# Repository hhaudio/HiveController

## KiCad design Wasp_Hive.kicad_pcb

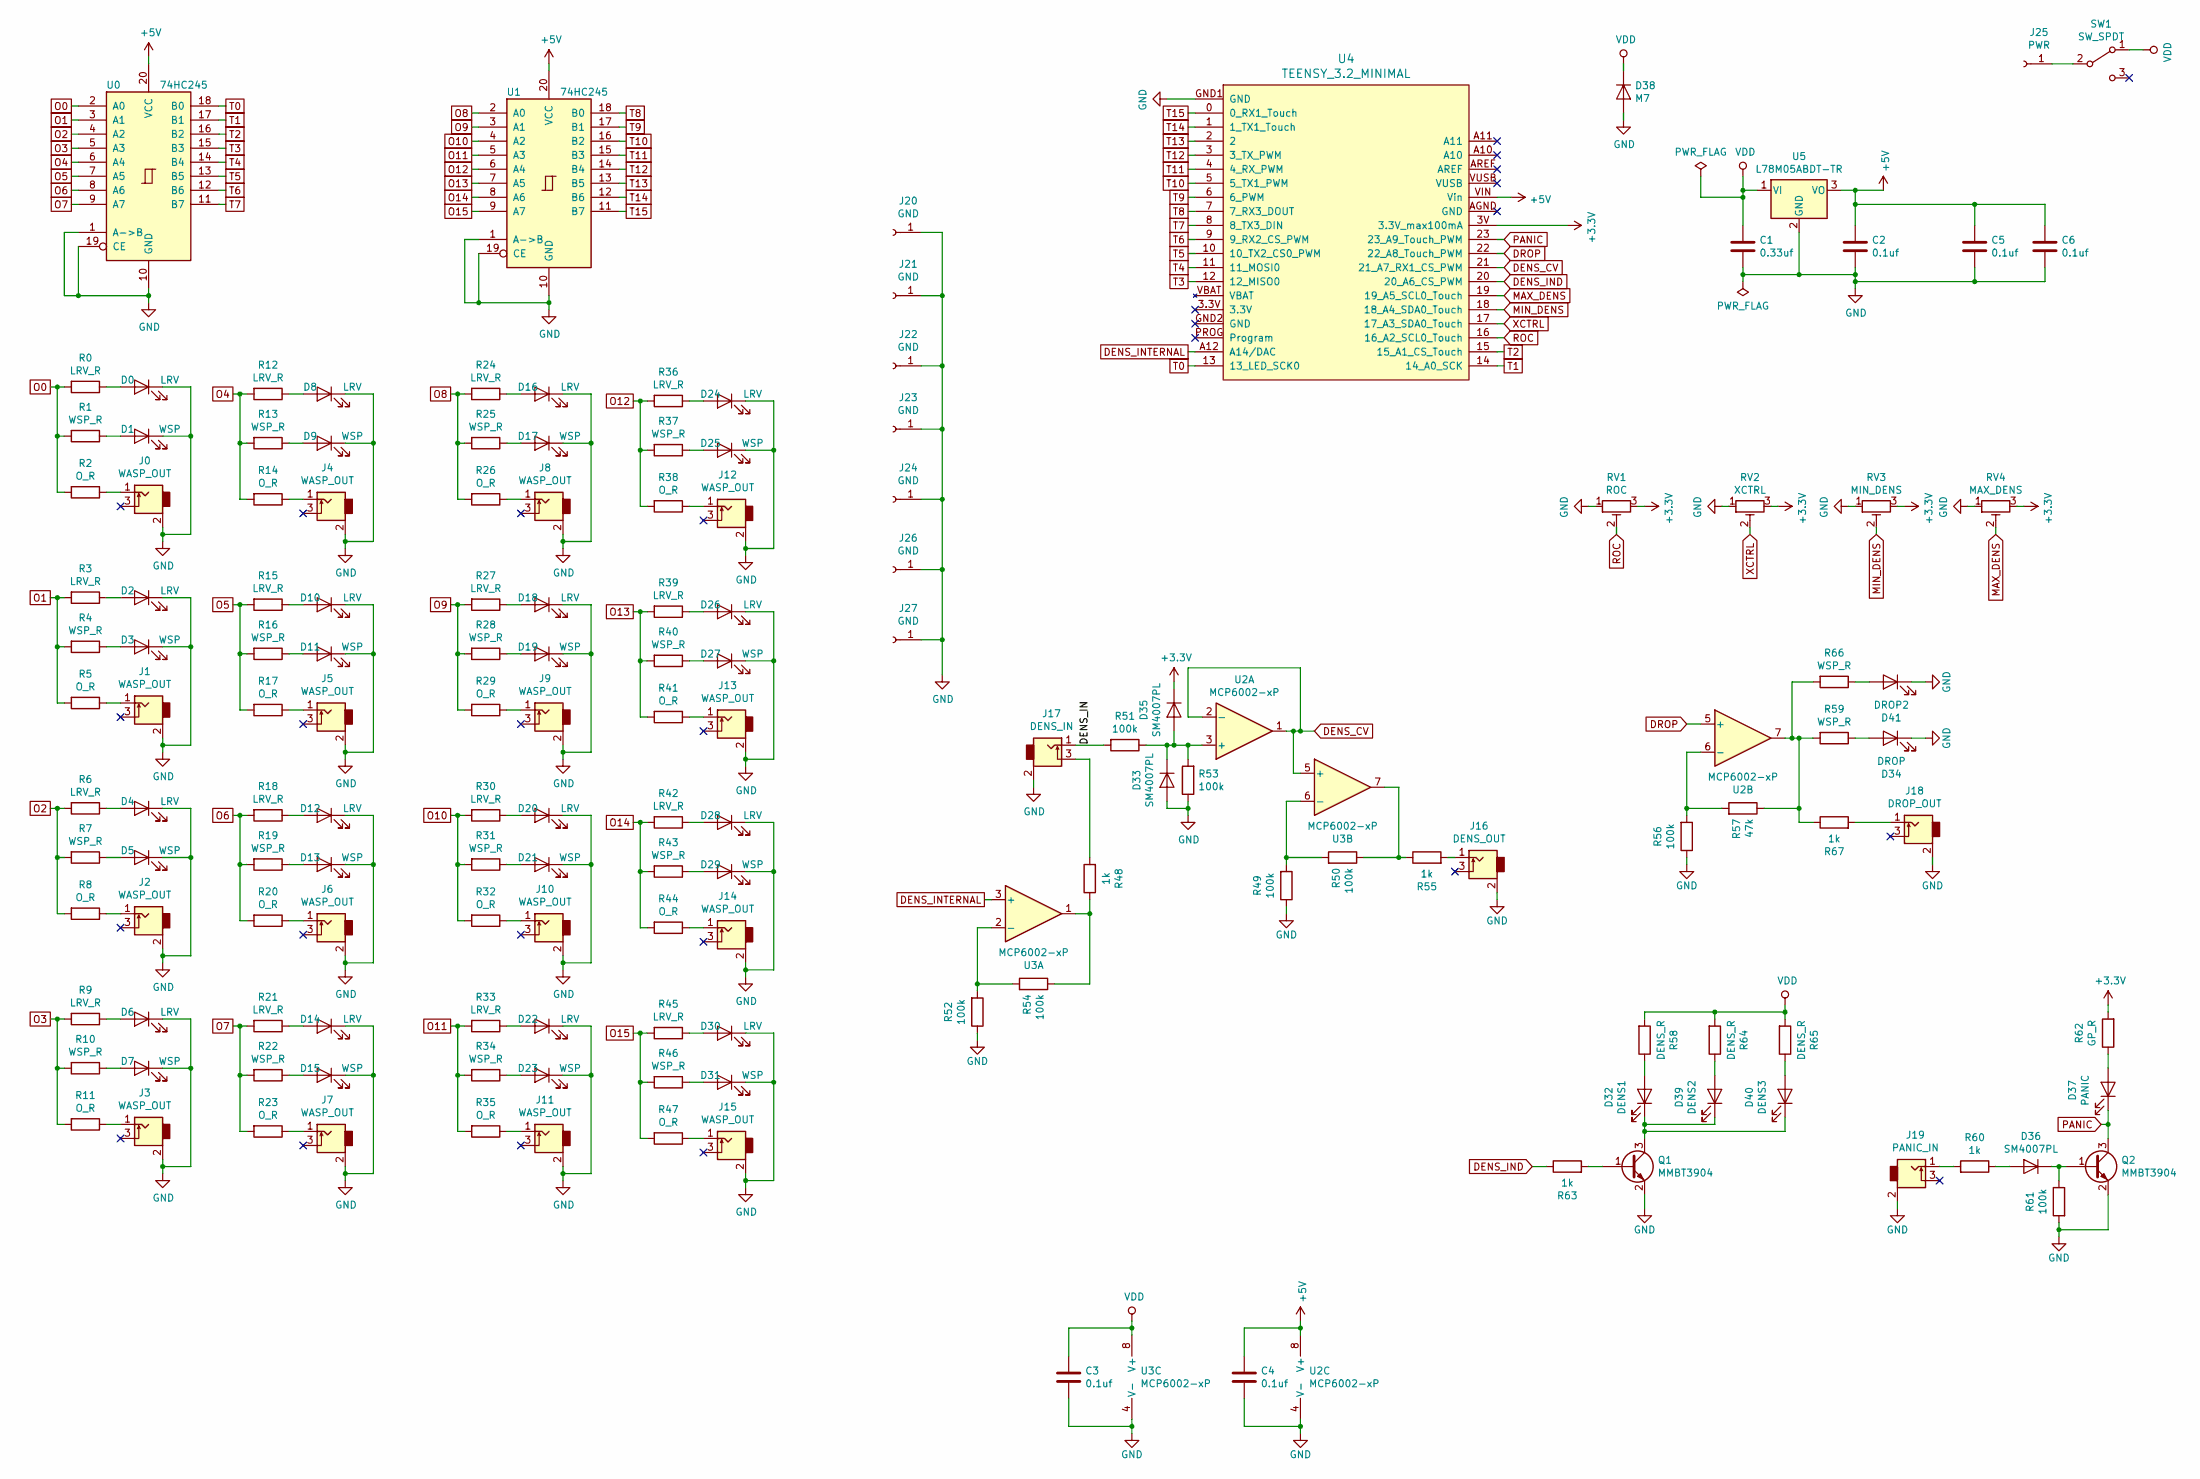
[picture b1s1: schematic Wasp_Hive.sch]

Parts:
C1: 0.33uf; C_0603_1608Metric_Pad1.05x0.95mm_HandSolder_SmallRef_Fab
C2, C3, C4, C5, C6: 0.1uf; C_0603_1608Metric_Pad1.05x0.95mm_HandSolder_SmallRef_Fab
D0, D2, D4, D6, D8, D10, D12, D14, D16, D18, D20, D22, D24, D26, D28, D30: LRV; Backlit_Larvae_Smaller
D1, D3, D5, D7, D9, D11, D13, D15, D17, D19, D21, D23, D25, D27, D29, D31: WSP; LED_1206_3216Metric_Pad1.42x1.75mm_HandSolder_FabRef
D32: DENS1; LED_1206_3216Metric_Pad1.42x1.75mm_HandSolder_FabRef
D33, D35, D36: SM4007PL; D_SOD-123
D34: DROP; LED_1206_3216Metric_Pad1.42x1.75mm_HandSolder_FabRef
D37: PANIC; LED_1206_3216Metric_Pad1.42x1.75mm_HandSolder_FabRef
D38: M7; D_SMA
D39: DENS2; LED_1206_3216Metric_Pad1.42x1.75mm_HandSolder_FabRef
D40: DENS3; LED_1206_3216Metric_Pad1.42x1.75mm_HandSolder_FabRef
D41: DROP2; LED_1206_3216Metric_Pad1.42x1.75mm_HandSolder_FabRef
J0, J1, J2, J3, J4, J5, J6, J7, J8, J9, J10, J11, J12, J13, J14, J15: WASP_OUT; EuroJack_Hex_SmallHoles_NoSilk_Clearance
J16: DENS_OUT; EuroJack_MonoSW_THT_NOREF_Mask_SmallHoles_NoSilk
J17: DENS_IN; EuroJack_MonoSW_THT_NOREF_Mask_SmallHoles_NoSilk
J18: DROP_OUT; EuroJack_MonoSW_THT_NOREF_Mask_SmallHoles_NoSilk
J19: PANIC_IN; EuroJack_MonoSW_THT_NOREF_Mask_SmallHoles_NoSilk
J20, J21, J22, J23, J24, J26, J27: GND; M3_Plated
J25: PWR; M3_Plated
Q1, Q2: MMBT3904; SOT-23
R0, R3, R6, R9, R12, R15, R18, R21, R24, R27, R30, R33, R36, R39, R42, R45: LRV_R; R_0603_1608Metric_Pad1.05x0.95mm_HandSolder_SmallRef_Fab
R1, R4, R7, R10, R13, R16, R19, R22, R25, R28, R31, R34, R37, R40, R43, R46, R59, R66: WSP_R; R_0603_1608Metric_Pad1.05x0.95mm_HandSolder_SmallRef_Fab
R2, R5, R8, R11, R14, R17, R20, R23, R26, R29, R32, R35, R38, R41, R44, R47: O_R; R_0603_1608Metric_Pad1.05x0.95mm_HandSolder_SmallRef_Fab
R48, R55, R60, R63, R67: 1k; R_0603_1608Metric_Pad1.05x0.95mm_HandSolder_SmallRef_Fab
R49, R50, R51, R52, R53, R54, R56, R61: 100k; R_0603_1608Metric_Pad1.05x0.95mm_HandSolder_SmallRef_Fab
R57: 47k; R_0603_1608Metric_Pad1.05x0.95mm_HandSolder_SmallRef_Fab
R58, R64, R65: DENS_R; R_0603_1608Metric_Pad1.05x0.95mm_HandSolder_SmallRef_Fab
R62: GP_R; R_0603_1608Metric_Pad1.05x0.95mm_HandSolder_SmallRef_Fab
RV1: ROC; SMD_TRIM_JLC
RV2: XCTRL; SMD_TRIM_JLC
RV3: MIN_DENS; SMD_TRIM_JLC
RV4: MAX_DENS; SMD_TRIM_JLC
SW1: SW_SPDT; Tayda_Slide_SPDT
U0, U1: 74HC245; SOIC-20W_7.5x12.8mm_P1.27mm
U2, U3: MCP6002-xP; SOIC-8_3.9x4.9mm_P1.27mm
U4: TEENSY_3.2_MINIMAL; TEENSY_LC_MIN_SILK_2SIDE
U5: L78M05ABDT-TR; TO-252-2

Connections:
+3V3: D35.1 (K), R62.2, RV1.3, RV2.3, RV3.3, RV4.3, U4.3V (3.3V_max100mA)
+5V: C2.1, C4.1, C5.1, C6.1, U0.20 (VCC), U1.20 (VCC), U2.8 (V+), U4.VIN (Vin), U5.3 (VO)
/DENS_IN: J17.1, R51.2
DENS_CV: U2.1, U2.2 (-), U3.5 (+), U4.21 (21_A7_RX1_CS_PWM)
DENS_IND: R63.1, U4.20 (20_A6_CS_PWM)
DENS_INTERNAL: U3.3 (+), U4.A12 (A14/DAC)
DROP: U2.5 (+), U4.22 (22_A8_Touch_PWM)
GND: C1.2, C2.2, C3.2, C4.2, C5.2, C6.2, D0.1 (K), D1.1 (K), D2.1 (K), D3.1 (K), D4.1 (K), D5.1 (K), D6.1 (K), D7.1 (K), D8.1 (K), D9.1 (K), D10.1 (K), D11.1 (K), D12.1 (K), D13.1 (K), D14.1 (K), D15.1 (K), D16.1 (K), D17.1 (K), D18.1 (K), D19.1 (K), D20.1 (K), D21.1 (K), D22.1 (K), D23.1 (K), D24.1 (K), D25.1 (K), D26.1 (K), D27.1 (K), D28.1 (K), D29.1 (K), D30.1 (K), D31.1 (K), D33.2 (A), D34.1 (K), D38.2 (A), D41.1 (K), J0.2, J1.2, J2.2, J3.2, J4.2, J5.2, J6.2, J7.2, J8.2, J9.2, J10.2, J11.2, J12.2, J13.2, J14.2, J15.2, J16.2, J17.2, J18.2, J19.2, J20.1, J21.1, J22.1, J23.1, J24.1, J26.1, J27.1, Q1.2 (E), Q2.2 (E), R49.1, R52.1, R53.1, R56.1, R61.2, RV1.1, RV2.1, RV3.1, RV4.1, U0.1 (A->B), U0.10 (GND), U0.19 (CE), U1.1 (A->B), U1.10 (GND), U1.19 (CE), U2.4 (V-), U3.4 (V-), U4.GND1 (GND), U5.2 (GND)
MAX_DENS: RV4.2, U4.19 (19_A5_SCL0_Touch)
MIN_DENS: RV3.2, U4.18 (18_A4_SDA0_Touch)
unnamed: D0.2 (A), R0.1
unnamed: D1.2 (A), R1.1
unnamed: D2.2 (A), R3.1
unnamed: D3.2 (A), R4.1
unnamed: D4.2 (A), R6.1
unnamed: D5.2 (A), R7.1
unnamed: D6.2 (A), R9.1
unnamed: D7.2 (A), R10.1
unnamed: D8.2 (A), R12.1
unnamed: D9.2 (A), R13.1
unnamed: D10.2 (A), R15.1
unnamed: D11.2 (A), R16.1
unnamed: D12.2 (A), R18.1
unnamed: D13.2 (A), R19.1
unnamed: D14.2 (A), R21.1
unnamed: D15.2 (A), R22.1
unnamed: D16.2 (A), R24.1
unnamed: D17.2 (A), R25.1
unnamed: D18.2 (A), R27.1
unnamed: D19.2 (A), R28.1
unnamed: D20.2 (A), R30.1
unnamed: D21.2 (A), R31.1
unnamed: D22.2 (A), R33.1
unnamed: D23.2 (A), R34.1
unnamed: D24.2 (A), R36.1
unnamed: D25.2 (A), R37.1
unnamed: D26.2 (A), R39.1
unnamed: D27.2 (A), R40.1
unnamed: D28.2 (A), R42.1
unnamed: D29.2 (A), R43.1
unnamed: D30.2 (A), R45.1
unnamed: D31.2 (A), R46.1
unnamed: D32.1 (K), D39.1 (K), D40.1 (K), Q1.3 (C)
unnamed: D32.2 (A), R58.1
unnamed: D33.1 (K), D35.2 (A), R51.1, R53.2, U2.3 (+)
unnamed: D34.2 (A), R59.1
unnamed: D36.1 (K), Q2.1 (B), R61.1
unnamed: D36.2 (A), R60.1
unnamed: D37.2 (A), R62.1
unnamed: D39.2 (A), R64.1
unnamed: D40.2 (A), R65.1
unnamed: D41.2 (A), R66.1
unnamed: J0.1, R2.1
unnamed: J1.1, R5.1
unnamed: J2.1, R8.1
unnamed: J3.1, R11.1
unnamed: J4.1, R14.1
unnamed: J5.1, R17.1
unnamed: J6.1, R20.1
unnamed: J7.1, R23.1
unnamed: J8.1, R26.1
unnamed: J9.1, R29.1
unnamed: J10.1, R32.1
unnamed: J11.1, R35.1
unnamed: J12.1, R38.1
unnamed: J13.1, R41.1
unnamed: J14.1, R44.1
unnamed: J15.1, R47.1
unnamed: J16.1, R55.2
unnamed: J17.3, R48.2
unnamed: J18.1, R67.2
unnamed: J19.1, R60.2
unnamed: J25.1, SW1.2 (B)
unnamed: Q1.1 (B), R63.2
unnamed: R48.1, R54.1, U3.1
unnamed: R49.2, R50.2, U3.6 (-)
unnamed: R50.1, R55.1, U3.7
unnamed: R52.2, R54.2, U3.2 (-)
unnamed: R56.2, R57.2, U2.6 (-)
unnamed: R57.1, R59.2, R66.2, R67.1, U2.7
O0: R0.2, R1.2, R2.2, U0.2 (A0)
O1: R3.2, R4.2, R5.2, U0.3 (A1)
O2: R6.2, R7.2, R8.2, U0.4 (A2)
O3: R9.2, R10.2, R11.2, U0.5 (A3)
O4: R12.2, R13.2, R14.2, U0.6 (A4)
O5: R15.2, R16.2, R17.2, U0.7 (A5)
O6: R18.2, R19.2, R20.2, U0.8 (A6)
O7: R21.2, R22.2, R23.2, U0.9 (A7)
O8: R24.2, R25.2, R26.2, U1.2 (A0)
O9: R27.2, R28.2, R29.2, U1.3 (A1)
O10: R30.2, R31.2, R32.2, U1.4 (A2)
O11: R33.2, R34.2, R35.2, U1.5 (A3)
O12: R36.2, R37.2, R38.2, U1.6 (A4)
O13: R39.2, R40.2, R41.2, U1.7 (A5)
O14: R42.2, R43.2, R44.2, U1.8 (A6)
O15: R45.2, R46.2, R47.2, U1.9 (A7)
PANIC: D37.1 (K), Q2.3 (C), U4.23 (23_A9_Touch_PWM)
ROC: RV1.2, U4.16 (16_A2_SCL0_Touch)
T0: U0.18 (B0), U4.13 (13_LED_SCK0)
T1: U0.17 (B1), U4.14 (14_A0_SCK)
T2: U0.16 (B2), U4.15 (15_A1_CS_Touch)
T3: U0.15 (B3), U4.12 (12_MISO0)
T4: U0.14 (B4), U4.11 (11_MOSI0)
T5: U0.13 (B5), U4.10 (10_TX2_CS0_PWM)
T6: U0.12 (B6), U4.9 (9_RX2_CS_PWM)
T7: U0.11 (B7), U4.8 (8_TX3_DIN)
T8: U1.18 (B0), U4.7 (7_RX3_DOUT)
T9: U1.17 (B1), U4.6 (6_PWM)
T10: U1.16 (B2), U4.5 (5_TX1_PWM)
T11: U1.15 (B3), U4.4 (4_RX_PWM)
T12: U1.14 (B4), U4.3 (3_TX_PWM)
T13: U1.13 (B5), U4.2
T14: U1.12 (B6), U4.1 (1_TX1_Touch)
T15: U1.11 (B7), U4.0 (0_RX1_Touch)
VDD: C1.1, C3.1, D38.1 (K), R58.2, R64.2, R65.2, SW1.1 (A), U3.8 (V+), U5.1 (VI)
XCTRL: RV2.2, U4.17 (17_A3_SDA0_Touch)

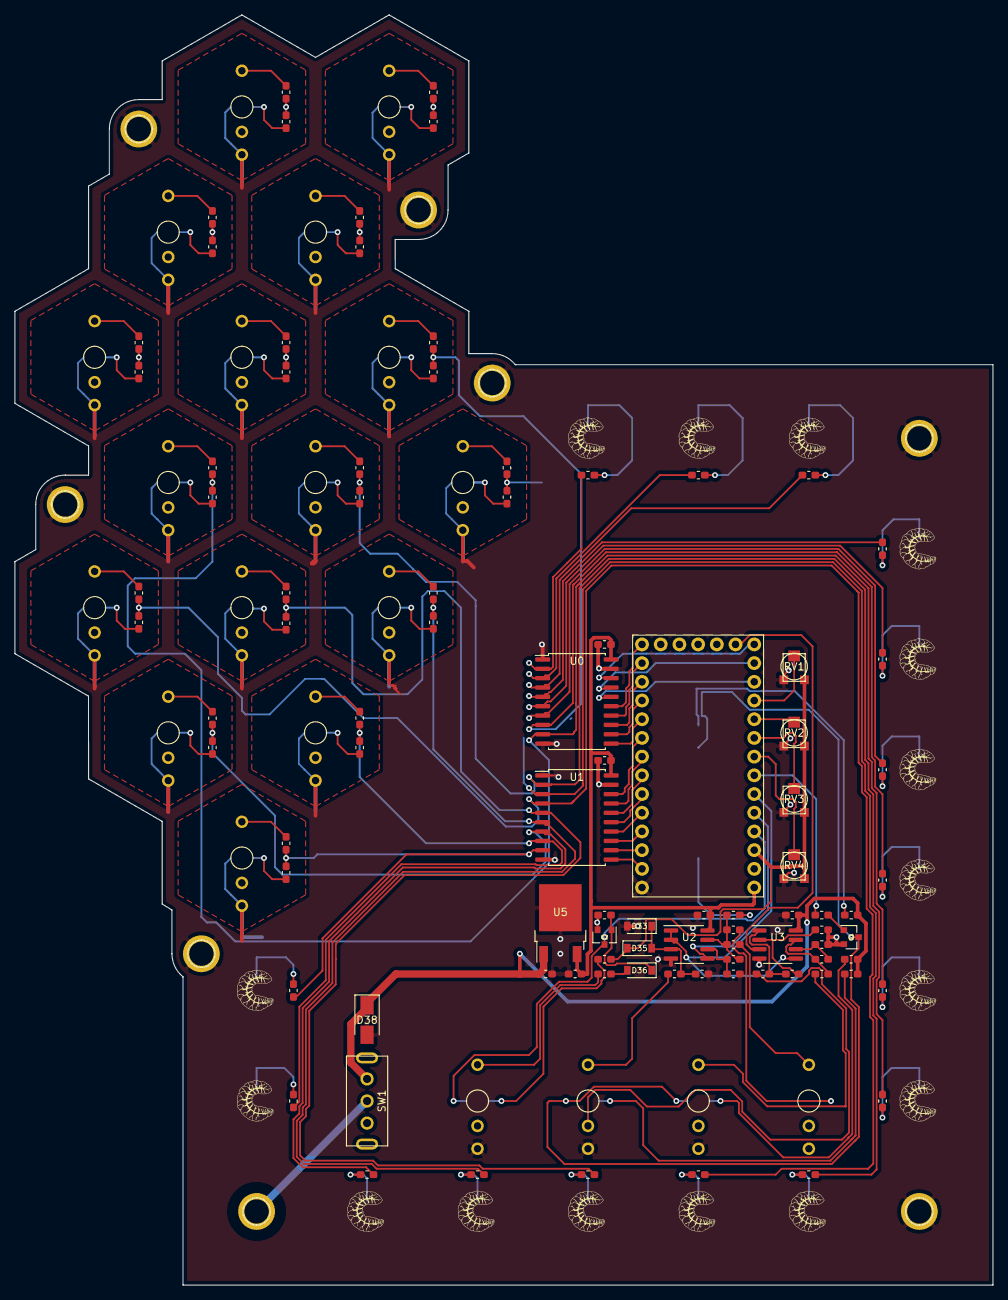
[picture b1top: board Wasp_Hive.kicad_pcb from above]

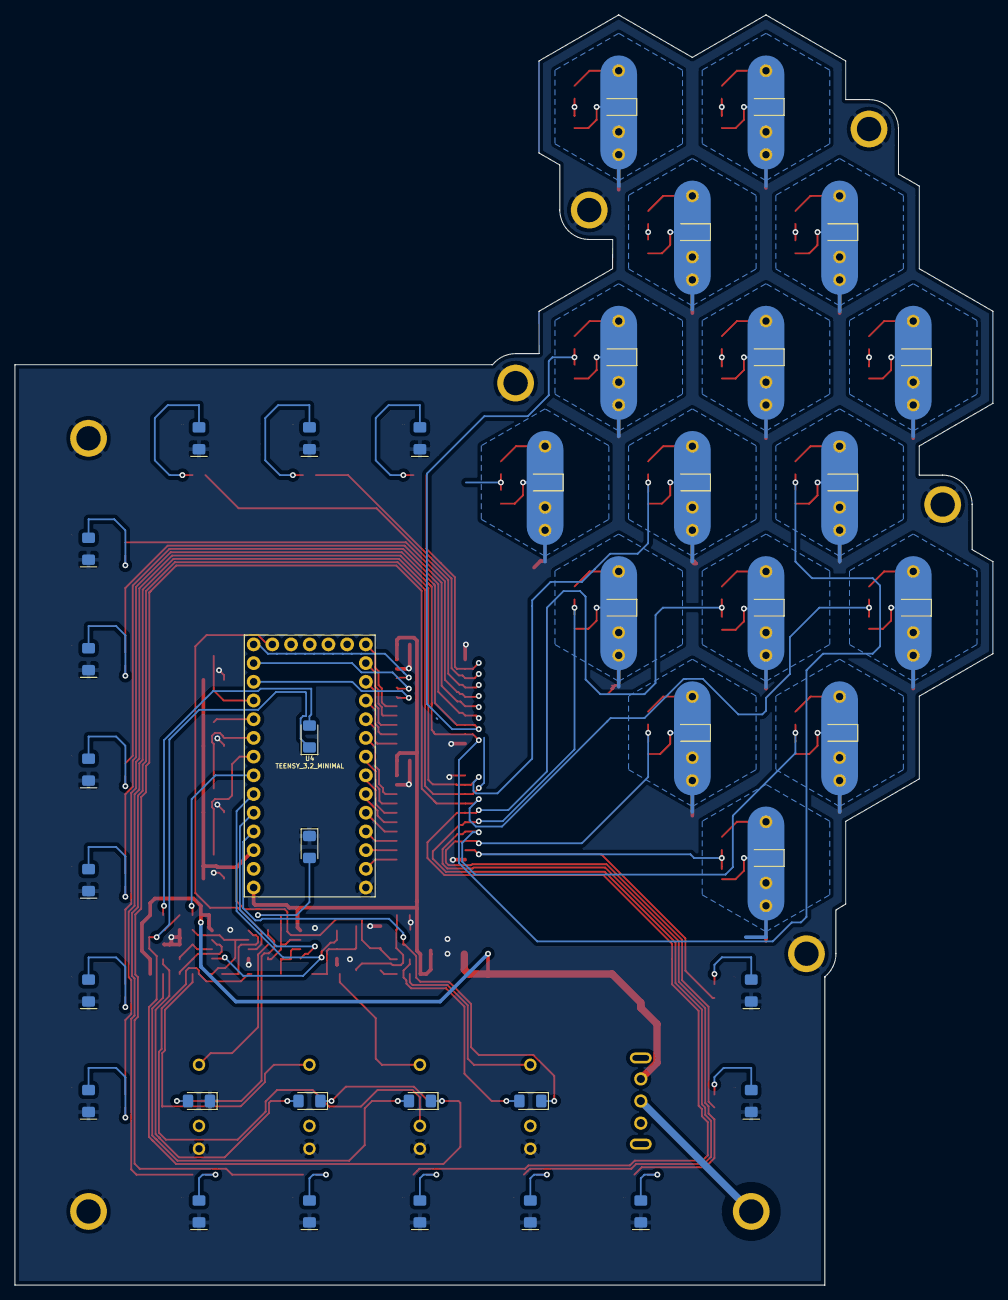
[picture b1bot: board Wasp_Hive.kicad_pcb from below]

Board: 2 copper layers, 132.8 x 172.5 mm, 157 parts (39 on the bottom side), 116 nets.

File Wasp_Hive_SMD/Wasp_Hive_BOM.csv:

Comment,Designator,Footprint,JLCPCB Part #（optional）
0.1uf,C2,C_0603_1608Metric_Pad1.05x0.95mm_HandSolder_SmallRef_Fab,C14663
0.1uf,C3,C_0603_1608Metric_Pad1.05x0.95mm_HandSolder_SmallRef_Fab,C14663
0.1uf,C4,C_0603_1608Metric_Pad1.05x0.95mm_HandSolder_SmallRef_Fab,C14663
0.1uf,C5,C_0603_1608Metric_Pad1.05x0.95mm_HandSolder_SmallRef_Fab,C14663
0.1uf,C6,C_0603_1608Metric_Pad1.05x0.95mm_HandSolder_SmallRef_Fab,C14663
0.33uf,C1,C_0603_1608Metric_Pad1.05x0.95mm_HandSolder_SmallRef_Fab,C1615
M7,D38,D_SMA,C95872
SM4007PL,D33,D_SOD-123,C64898
SM4007PL,D35,D_SOD-123,C64898
SM4007PL,D36,D_SOD-123,C64898
100k,R49,R_0603_1608Metric_Pad1.05x0.95mm_HandSolder_SmallRef_Fab,C25803
100k,R50,R_0603_1608Metric_Pad1.05x0.95mm_HandSolder_SmallRef_Fab,C25803
100k,R51,R_0603_1608Metric_Pad1.05x0.95mm_HandSolder_SmallRef_Fab,C25803
100k,R52,R_0603_1608Metric_Pad1.05x0.95mm_HandSolder_SmallRef_Fab,C25803
100k,R53,R_0603_1608Metric_Pad1.05x0.95mm_HandSolder_SmallRef_Fab,C25803
100k,R54,R_0603_1608Metric_Pad1.05x0.95mm_HandSolder_SmallRef_Fab,C25803
100k,R56,R_0603_1608Metric_Pad1.05x0.95mm_HandSolder_SmallRef_Fab,C25803
100k,R61,R_0603_1608Metric_Pad1.05x0.95mm_HandSolder_SmallRef_Fab,C25803
1k,R48,R_0603_1608Metric_Pad1.05x0.95mm_HandSolder_SmallRef_Fab,C21190
1k,R55,R_0603_1608Metric_Pad1.05x0.95mm_HandSolder_SmallRef_Fab,C21190
1k,R60,R_0603_1608Metric_Pad1.05x0.95mm_HandSolder_SmallRef_Fab,C21190
1k,R63,R_0603_1608Metric_Pad1.05x0.95mm_HandSolder_SmallRef_Fab,C21190
1k,R67,R_0603_1608Metric_Pad1.05x0.95mm_HandSolder_SmallRef_Fab,C21190
47k,R57,R_0603_1608Metric_Pad1.05x0.95mm_HandSolder_SmallRef_Fab,C25819
DENS_R,R58,R_0603_1608Metric_Pad1.05x0.95mm_HandSolder_SmallRef_Fab,C22975
DENS_R,R64,R_0603_1608Metric_Pad1.05x0.95mm_HandSolder_SmallRef_Fab,C22975
DENS_R,R65,R_0603_1608Metric_Pad1.05x0.95mm_HandSolder_SmallRef_Fab,C22975
GP_R,R62,R_0603_1608Metric_Pad1.05x0.95mm_HandSolder_SmallRef_Fab,C22775
LRV_R,R0,R_0603_1608Metric_Pad1.05x0.95mm_HandSolder_SmallRef_Fab,C23179
LRV_R,R12,R_0603_1608Metric_Pad1.05x0.95mm_HandSolder_SmallRef_Fab,C23179
LRV_R,R15,R_0603_1608Metric_Pad1.05x0.95mm_HandSolder_SmallRef_Fab,C23179
LRV_R,R18,R_0603_1608Metric_Pad1.05x0.95mm_HandSolder_SmallRef_Fab,C23179
LRV_R,R21,R_0603_1608Metric_Pad1.05x0.95mm_HandSolder_SmallRef_Fab,C23179
LRV_R,R24,R_0603_1608Metric_Pad1.05x0.95mm_HandSolder_SmallRef_Fab,C23179
LRV_R,R27,R_0603_1608Metric_Pad1.05x0.95mm_HandSolder_SmallRef_Fab,C23179
LRV_R,R3,R_0603_1608Metric_Pad1.05x0.95mm_HandSolder_SmallRef_Fab,C23179
LRV_R,R30,R_0603_1608Metric_Pad1.05x0.95mm_HandSolder_SmallRef_Fab,C23179
LRV_R,R33,R_0603_1608Metric_Pad1.05x0.95mm_HandSolder_SmallRef_Fab,C23179
LRV_R,R36,R_0603_1608Metric_Pad1.05x0.95mm_HandSolder_SmallRef_Fab,C23179
LRV_R,R39,R_0603_1608Metric_Pad1.05x0.95mm_HandSolder_SmallRef_Fab,C23179
LRV_R,R42,R_0603_1608Metric_Pad1.05x0.95mm_HandSolder_SmallRef_Fab,C23179
LRV_R,R45,R_0603_1608Metric_Pad1.05x0.95mm_HandSolder_SmallRef_Fab,C23179
LRV_R,R6,R_0603_1608Metric_Pad1.05x0.95mm_HandSolder_SmallRef_Fab,C23179
LRV_R,R9,R_0603_1608Metric_Pad1.05x0.95mm_HandSolder_SmallRef_Fab,C23179
O_R,R11,R_0603_1608Metric_Pad1.05x0.95mm_HandSolder_SmallRef_Fab,C21190
O_R,R14,R_0603_1608Metric_Pad1.05x0.95mm_HandSolder_SmallRef_Fab,C21190
O_R,R17,R_0603_1608Metric_Pad1.05x0.95mm_HandSolder_SmallRef_Fab,C21190
O_R,R2,R_0603_1608Metric_Pad1.05x0.95mm_HandSolder_SmallRef_Fab,C21190
O_R,R20,R_0603_1608Metric_Pad1.05x0.95mm_HandSolder_SmallRef_Fab,C21190
O_R,R23,R_0603_1608Metric_Pad1.05x0.95mm_HandSolder_SmallRef_Fab,C21190
O_R,R26,R_0603_1608Metric_Pad1.05x0.95mm_HandSolder_SmallRef_Fab,C21190
O_R,R29,R_0603_1608Metric_Pad1.05x0.95mm_HandSolder_SmallRef_Fab,C21190
O_R,R32,R_0603_1608Metric_Pad1.05x0.95mm_HandSolder_SmallRef_Fab,C21190
O_R,R35,R_0603_1608Metric_Pad1.05x0.95mm_HandSolder_SmallRef_Fab,C21190
O_R,R38,R_0603_1608Metric_Pad1.05x0.95mm_HandSolder_SmallRef_Fab,C21190
O_R,R41,R_0603_1608Metric_Pad1.05x0.95mm_HandSolder_SmallRef_Fab,C21190
O_R,R44,R_0603_1608Metric_Pad1.05x0.95mm_HandSolder_SmallRef_Fab,C21190
O_R,R47,R_0603_1608Metric_Pad1.05x0.95mm_HandSolder_SmallRef_Fab,C21190
O_R,R5,R_0603_1608Metric_Pad1.05x0.95mm_HandSolder_SmallRef_Fab,C21190
O_R,R8,R_0603_1608Metric_Pad1.05x0.95mm_HandSolder_SmallRef_Fab,C21190
WSP_R,R1,R_0603_1608Metric_Pad1.05x0.95mm_HandSolder_SmallRef_Fab,C23179
WSP_R,R10,R_0603_1608Metric_Pad1.05x0.95mm_HandSolder_SmallRef_Fab,C23179
WSP_R,R13,R_0603_1608Metric_Pad1.05x0.95mm_HandSolder_SmallRef_Fab,C23179
WSP_R,R16,R_0603_1608Metric_Pad1.05x0.95mm_HandSolder_SmallRef_Fab,C23179
WSP_R,R19,R_0603_1608Metric_Pad1.05x0.95mm_HandSolder_SmallRef_Fab,C23179
WSP_R,R22,R_0603_1608Metric_Pad1.05x0.95mm_HandSolder_SmallRef_Fab,C23179
WSP_R,R25,R_0603_1608Metric_Pad1.05x0.95mm_HandSolder_SmallRef_Fab,C23179
WSP_R,R28,R_0603_1608Metric_Pad1.05x0.95mm_HandSolder_SmallRef_Fab,C23179
WSP_R,R31,R_0603_1608Metric_Pad1.05x0.95mm_HandSolder_SmallRef_Fab,C23179
WSP_R,R34,R_0603_1608Metric_Pad1.05x0.95mm_HandSolder_SmallRef_Fab,C23179
WSP_R,R37,R_0603_1608Metric_Pad1.05x0.95mm_HandSolder_SmallRef_Fab,C23179
WSP_R,R4,R_0603_1608Metric_Pad1.05x0.95mm_HandSolder_SmallRef_Fab,C23179
WSP_R,R40,R_0603_1608Metric_Pad1.05x0.95mm_HandSolder_SmallRef_Fab,C23179
WSP_R,R43,R_0603_1608Metric_Pad1.05x0.95mm_HandSolder_SmallRef_Fab,C23179
WSP_R,R46,R_0603_1608Metric_Pad1.05x0.95mm_HandSolder_SmallRef_Fab,C23179
WSP_R,R59,R_0603_1608Metric_Pad1.05x0.95mm_HandSolder_SmallRef_Fab,C23179
WSP_R,R66,R_0603_1608Metric_Pad1.05x0.95mm_HandSolder_SmallRef_Fab,C23179
WSP_R,R7,R_0603_1608Metric_Pad1.05x0.95mm_HandSolder_SmallRef_Fab,C23179
MAX_DENS,RV4,SMD_TRIM_JLC,C128550
MIN_DENS,RV3,SMD_TRIM_JLC,C128550
ROC,RV1,SMD_TRIM_JLC,C128550
XCTRL,RV2,SMD_TRIM_JLC,C128550
74HC245,U0,SOIC-20W_7.5x12.8mm_P1.27mm,C5625
74HC245,U1,SOIC-20W_7.5x12.8mm_P1.27mm,C5625
MCP6002-xP,U2,SOIC-8_3.9x4.9mm_P1.27mm,C7377
MCP6002-xP,U3,SOIC-8_3.9x4.9mm_P1.27mm,C7377
MMBT3904,Q1,SOT-23,C20526
MMBT3904,Q2,SOT-23,C20526
L78M05ABDT-TR,U5,TO-252-2,C58069

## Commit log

2021-11-17 started sketch:
2021-11-17 first form factor
2021-11-18 alterantive sketch
2021-11-18 Finished schematic
2021-11-28 layout ideas
2021-11-29 layout progress
2021-11-29 layout
2021-11-30 alt layout
2021-11-30 commit before trying shit
2021-11-30 slightly higher
2021-11-30 breaking for night
2021-11-30 trying border
2021-11-30 border looks good
2021-11-30 doing traces
2021-11-30 footprint update
2021-12-01 layout almost done
2021-12-02 autorouter method
2021-12-02 better router
2021-12-02 not working
2022-02-25 schematic
